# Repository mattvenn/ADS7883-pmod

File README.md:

# PMOD 2 x ADS7883 ADC

the ADS7883 is a 12 bit, serial ADC. It can sample up to 3MHz, and can be supplied up to 5v.

It needs 3 pins to operate: clk, select and data.

Supply can be 3.3v from the PMOD (limits maximum range of ADC to 3.3v), or 5v with a 
precision regulator and an external supply between 5.5v and 16v.

Use the ext/pmod jumper to select the source.

# Gerbers

## [fab-ADS7883-pmod-2018-07-02.zip](fab-ADS7883-pmod-2018-07-02.zip)

The silkscreen has an error on the 2 inputs. The 0v and ADC inputs are reversed. Attach 0v to ADC and ADC input to 0v.

## [fab-ADS7883-pmod-2018-07-30.zip](fab-ADS7883-pmod-2018-07-30.zip)

Fixes the reversed input labels.

# BOM

If you are using PMOD 3.3v for supply, you don't need C7, U1, C5.

LED D1 and R2 are optional for indicating PSU is good.

C1 to C4 are bypass caps and will help to improve noise performance if added.

* ADC1 and 2: ADS7883 http://es.farnell.com/texas-instruments/ads7883sbdbvt/adc-sar-12bit-3msps-6sot23/dp/2082426
* U1: ref5050 http://es.farnell.com/texas-instruments/ref5050aidg4/ref-de-tensi-n-serie-5v-soic-8/dp/1439628

# Verilog Core

[icestick/adc.v](adc.v) is tested Verilog for the ADC.

A working demo for the icestick is provided in the [icestick](icestick) directory. This reads ADC1 and shows top 5 bits on the icestick's LEDs.

To synthesise and program an attached icestick using the Icestorm tools:

    make prog

To simulate using iverilog and launch gtkwave to view the waveforms:

    make debug-adc

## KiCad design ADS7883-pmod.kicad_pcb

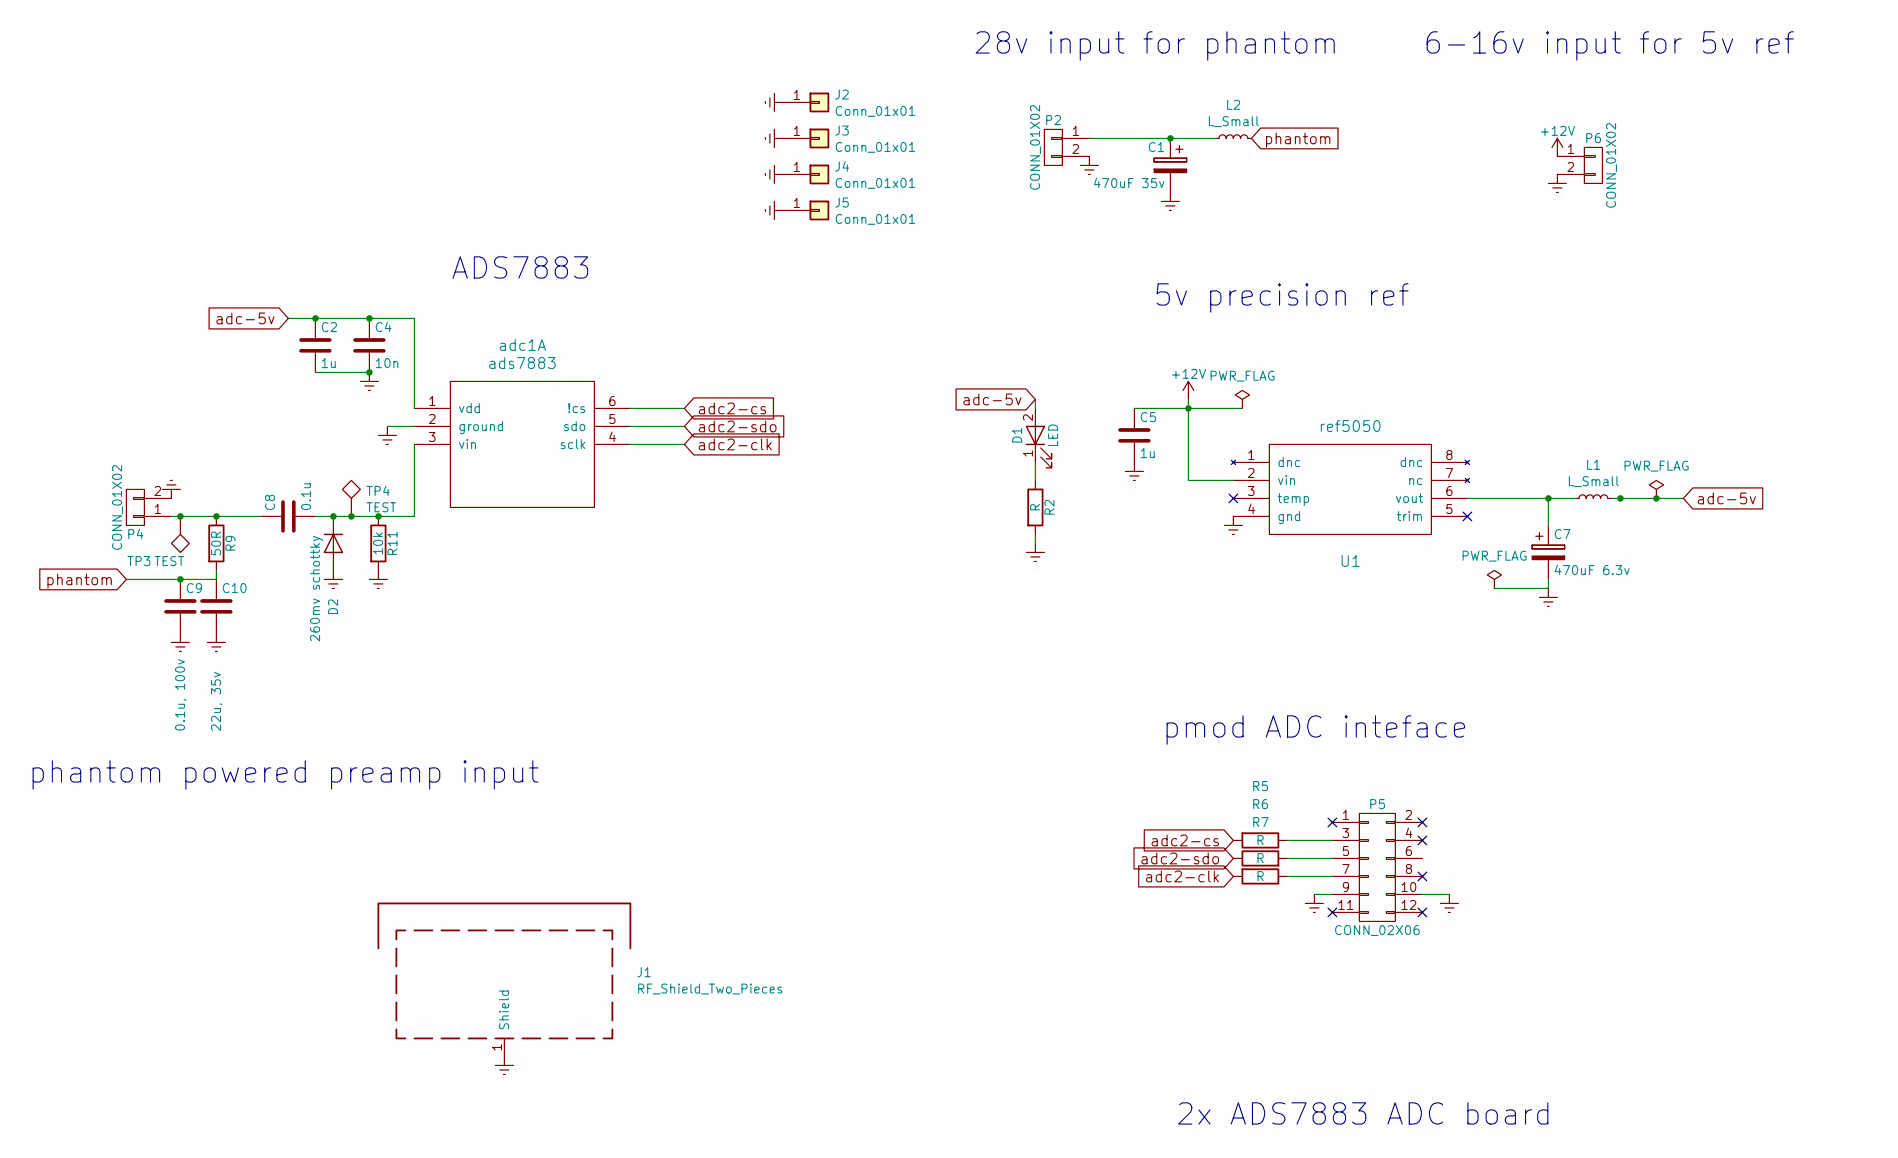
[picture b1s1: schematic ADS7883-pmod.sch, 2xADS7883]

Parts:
C1: 470uF 35v; CP_Elec_10x10; farnell # 2507737
C2, C5: 1u; C_0603_HandSoldering
C4: 10n; C_0603_HandSoldering
C7: 470uF 6.3v; CP_Elec_6.3x7.7; farnell # 2065955
C8: 0.1u; C_0603_HandSoldering
C9: 0.1u, 100v; C_0603_HandSoldering
C10: 22u, 35v; CP_Tantalum_Case-D_EIA-7343-31_Hand; farnell # 1457504
D1: LED; LED_0603_HandSoldering
D2: 260mv schottky; D_SOT-23_ANK; farnell # 1081206
J1: RF_Shield_Two_Pieces; Laird_Technologies_BMI-S-102_16.50x16.50mm; farnell # 2497717
J2, J3, J4, J5: Conn_01x01; MountingHole_3.2mm_M3_DIN965_Pad
L1, L2: L_Small; L_0603_HandSoldering
P2, P6: CONN_01X02; Pin_Header_Straight_1x02
P4: CONN_01X02; CON-SMA-EDGE
P5: CONN_02X06; Pin_Header_Straight_2x06
R2, R5, R6, R7: R; C_0603_HandSoldering
R9: 50R; R_1206_HandSoldering
R11: 10k; C_0603_HandSoldering
TP3, TP4: TEST; Test_Point_Pad_1.0x1.0mm
U1: ref5050; SOIC-8_3.9x4.9mm_Pitch1.27mm; farnell # 1439628
adc1: ads7883; SOT-23-6; farnell # 2082426

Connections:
+12V: C5.1, P6.1, U1.2 (vin)
Earth: C1.2, C2.2, C4.2, C5.2, C7.2, C9.2, C10.2, D2.2 (A), J1.1, J2.1, J3.1, J4.1, J5.1, P2.2, P4.2, P5.9, P5.10, P6.2, R2.2, R11.2, U1.4 (gnd), adc1.2 (ground)
unnamed: C1.1, L2.2, P2.1
unnamed: C7.1, L1.1, U1.6 (vout)
unnamed: C8.1, P4.1, R9.1, TP3.1
unnamed: C8.2, D2.1 (K), R11.1, TP4.1, adc1.3 (vin)
unnamed: D1.1 (K), R2.1
unnamed: P5.3, R5.1
unnamed: P5.5, R6.2
unnamed: P5.7, R7.1
adc2-clk: R7.2, adc1.4 (sclk)
adc2-cs: R5.2, adc1.6 (!cs)
adc2-sdo: R6.1, adc1.5 (sdo)
adc-5v: C2.1, C4.1, D1.2 (A), L1.2, adc1.1 (vdd)
phantom: C9.1, C10.1, L2.1, R9.2

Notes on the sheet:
2x ADS7883 ADC board
28v input for phantom
6-16v input for 5v ref
5v precision ref
pmod ADC inteface
ADS7883
phantom powered preamp input

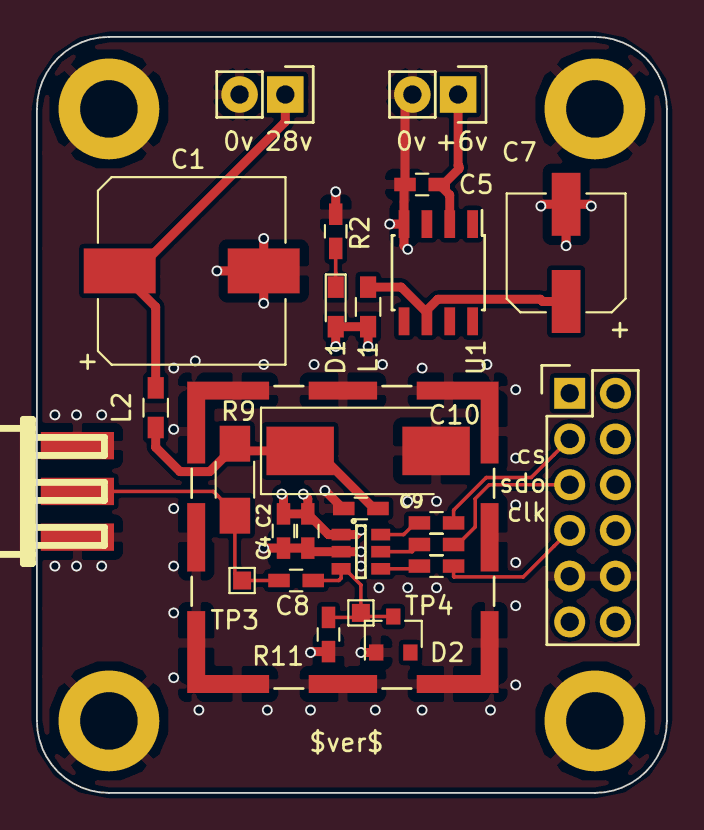
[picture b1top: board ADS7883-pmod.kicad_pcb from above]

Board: 4 copper layers, 35.0 x 42.0 mm, 31 parts (0 on the bottom side), 15 nets.

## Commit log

2018-07-02 ads7883 pmod breakout first commit
2018-07-28 fix board for printing
2018-07-28 updated docs
2018-07-30 both ADCs do not share a clock
2018-07-30 icestick example
2018-07-30 fix reverse input labels
2019-04-25 convert to 4 layers and improve routing
2019-04-26 got rid of 1 ADC and added phantom and shield can
